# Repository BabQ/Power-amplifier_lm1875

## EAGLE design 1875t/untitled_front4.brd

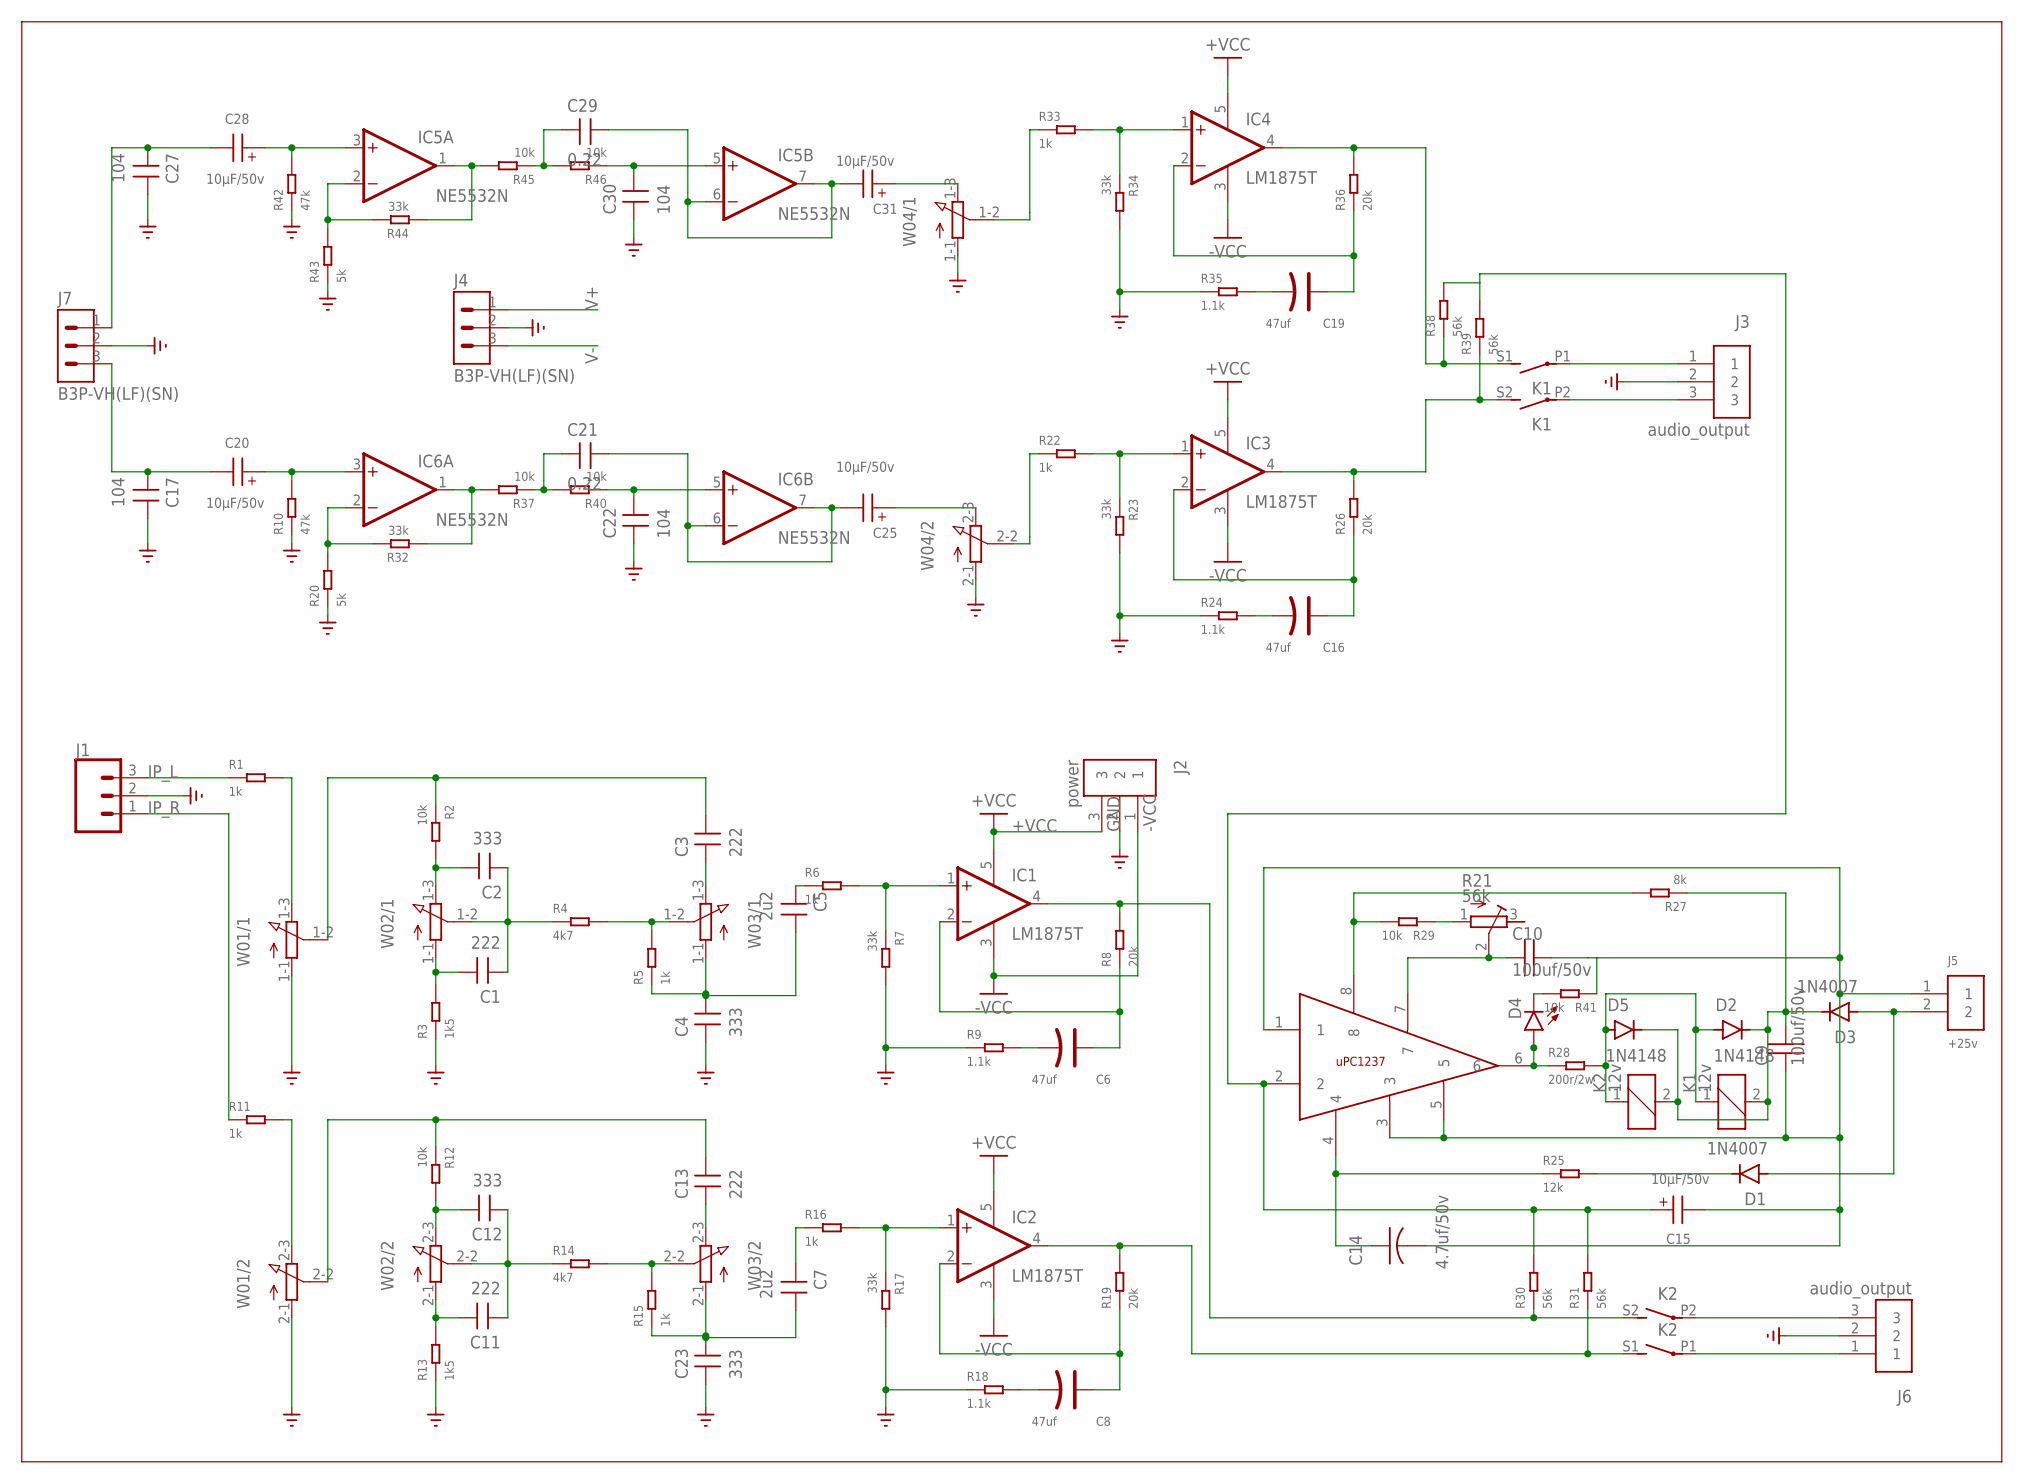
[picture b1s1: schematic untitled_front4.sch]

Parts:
C1, C3, C11, C13: 222; 5.08MM-独石电容
C2, C4, C12, C23: 333; 5.08MM-独石电容
C5, C7: 2u2; 5.08MM-独石电容
C6, C8, C16, C19: 47uf; PC-D5.3MM
C9, C10: 100uf/50v; 8X12
C14: 4.7uf/50v; CAP_RADIAL_2MM
C15, C20, C25, C28, C31: 10µF/50v; WCAP-AT1H_5X11(DXL)
C17, C22, C27, C30: 104; 5.08MM-独石电容
C21, C29: 0.22; 5.08MM-独石电容
D1, D3: 1N4007; DO-41
D2, D5: 1N4148; DO-41
D4: BEAGLEBONE_BLUE_LED-3MM-NO_SILK; BEAGLEBONE_BLUE_BEAGLEBONE_BLUE_LED3MM-NS
IC1, IC2, IC3, IC4: LM1875T; CB367
IC5, IC6: NE5532N; DIL08
J1: CONN_03POLAR; MOLEX-1X3
J2: power; TERMINALBLOCK_PLUGGABLE-3-7.62MM
J3, J6: audio_output; TERMINALBLOCK_PLUGGABLE-3-7.62MM
J4, J7: B3P-VH(LF)(SN); HDR-03
J5: +25v; S2B-PH-K-S(LF)(SN)
K1, K2: 12v; G2R2A
R1, R5, R6, R11, R15, R16, R22, R33: 1k; PR-D2.3XL6.5MM
R2, R12, R29, R37, R40, R41, R45, R46: 10k; PR-D2.3XL6.5MM
R3, R13: 1k5; PR-D2.3XL6.5MM
R4, R14: 4k7; PR-D2.3XL6.5MM
R7, R17, R23, R32, R34, R44: 33k; PR-D2.3XL6.5MM
R8, R19, R26, R36: 20k; PR-D2.3XL6.5MM
R9, R18, R24, R35: 1.1k; PR-D2.3XL6.5MM
R10, R42: 47k; PR-D2.3XL6.5MM
R20, R43: 5k; PR-D2.3XL6.5MM
R21: 56k; RTRIM3296W
R25: 12k; PR-D2.3XL6.5MM
R27: 8k; PR-D2.3XL6.5MM
R28: 200r/2w; PR-D2.3XL6.5MM
R30, R31, R38, R39: 56k; PR-D2.3XL6.5MM
U2: UPC1237HA; SIP8
W01, W02, W03, W04: 3RP/1610G

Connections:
+VCC: IC1.5 (V+), IC2.5 (V+), IC3.5 (V+), IC4.5 (V+), J2.3
-VCC: IC1.3 (V-), IC2.3 (V-), IC3.3 (V-), IC4.3 (V-), J2.1
GND: C4.P$2 (1), C17.P$1 (2), C22.P$2 (1), C23.P$2 (1), C27.P$1 (2), C30.P$2 (1), J1.2, J2.2, J3.2, J4.2, J6.2, J7.2, R3.1, R7.2, R9.1, R10.1, R13.1, R17.2, R18.1, R20.1, R23.2, R24.1, R34.2, R35.1, R42.1, R43.1, W01.1-1 (A), W01.2-1 (A), W04.1-1 (A), W04.2-1 (A)
IP_L: J1.3, R1.1
IP_R: J1.1, R11.1
unnamed: R1.2, W01.1-3 (E)
unnamed: D4.K (C), R41.2
unnamed: C2.P$1 (2), R2.2, W02.1-3 (E)
unnamed: C1.P$1 (2), R3.2, W02.1-1 (A)
unnamed: R4.2, R5.2, W03.1-2 (S)
unnamed: C1.P$2 (1), C2.P$2 (1), R4.1, W02.1-2 (S)
unnamed: IC1.1 (+IN), R6.2, R7.1
unnamed: C4.P$1 (2), C5.P$1 (2), R5.1, W03.1-1 (A)
unnamed: IC1.4 (OUT), K2.S2 (S), R8.2, R30.1
unnamed: C6.+, IC1.2 (-IN), R8.1
unnamed: C5.P$2 (1), R6.1
unnamed: C6.-, R9.2
unnamed: C17.P$2 (1), C20.2 (-), J7.3
unnamed: C3.P$2 (1), W03.1-3 (E)
unnamed: R11.2, W01.2-3 (E)
unnamed: C27.P$2 (1), C28.2 (-), J7.1
unnamed: C12.P$1 (2), R12.2, W02.2-3 (E)
unnamed: C11.P$1 (2), R13.2, W02.2-1 (A)
unnamed: R14.2, R15.2, W03.2-2 (S)
unnamed: C11.P$2 (1), C12.P$2 (1), R14.1, W02.2-2 (S)
unnamed: C7.P$1 (2), C23.P$1 (2), R15.1, W03.2-1 (A)
unnamed: IC2.1 (+IN), R16.2, R17.1
unnamed: IC2.4 (OUT), K2.S1 (S), R19.2, R31.1
unnamed: C8.+, IC2.2 (-IN), R19.1
unnamed: C7.P$2 (1), R16.1
unnamed: C8.-, R18.2
unnamed: C20.1 (+), IC6.3 (+IN), R10.2
unnamed: C13.P$2 (1), W03.2-3 (E)
unnamed: J6.1, K2.P1
unnamed: J6.3, K2.P2
unnamed: D1.C, R25.2
unnamed: C10.1, R21.2 (S), U2.7
unnamed: R33.1, W04.1-2 (S)
unnamed: IC3.1 (+IN), R22.2, R23.1
unnamed: IC3.4 (OUT), K1.S2 (S), R26.2, R39.1
unnamed: C16.+, IC3.2 (-IN), R26.1
unnamed: R22.1, W04.2-2 (S)
unnamed: C16.-, R24.2
unnamed: IC6.2 (-IN), R20.2, R32.2
unnamed: D1.A, D3.A, J5.2
unnamed: D4.A, R28.1, U2.6
unnamed: D2.A, D5.A, K1.1, K2.1, R28.2
unnamed: C9.2, D2.C, D3.C, D5.C, K1.2, K2.2, R27.1
unnamed: R27.2, R29.2, U2.8
unnamed: R21.1 (A), R29.1
unnamed: J3.3, K1.P2
unnamed: C14.1, R25.1, U2.4
unnamed: C15.1 (+), R30.2, R31.2, R38.2, R39.2, U2.2
unnamed: C28.1 (+), IC5.3 (+IN), R42.2
unnamed: IC4.1 (+IN), R33.2, R34.1
unnamed: IC4.4 (OUT), K1.S1 (S), R36.2, R38.1
unnamed: C19.+, IC4.2 (-IN), R36.1
unnamed: C3.P$1 (2), R2.1, W01.1-2 (S)
unnamed: C19.-, R35.2
unnamed: IC6.1 (OUT), R32.1, R37.2
unnamed: C9.1, C10.2, C14.2, C15.2 (-), J5.1, R41.1, U2.1, U2.3, U2.5
unnamed: J3.1, K1.P1
unnamed: C13.P$1 (2), R12.1, W01.2-2 (S)
unnamed: C21.P$2 (1), R37.1, R40.2
unnamed: C22.P$1 (2), IC6.5 (+IN), R40.1
unnamed: C21.P$1 (2), C25.2 (-), IC6.6 (-IN), IC6.7 (OUT)
unnamed: C29.P$1 (2), C31.2 (-), IC5.6 (-IN), IC5.7 (OUT)
unnamed: IC5.2 (-IN), R43.2, R44.2
unnamed: IC5.1 (OUT), R44.1, R45.2
unnamed: C29.P$2 (1), R45.1, R46.2
unnamed: C30.P$1 (2), IC5.5 (+IN), R46.1
unnamed: C31.1 (+), W04.1-3 (E)
unnamed: C25.1 (+), W04.2-3 (E)
V+: IC5.8 (V+), IC6.8 (V+), J4.1
V-: IC5.4 (V-), IC6.4 (V-), J4.3

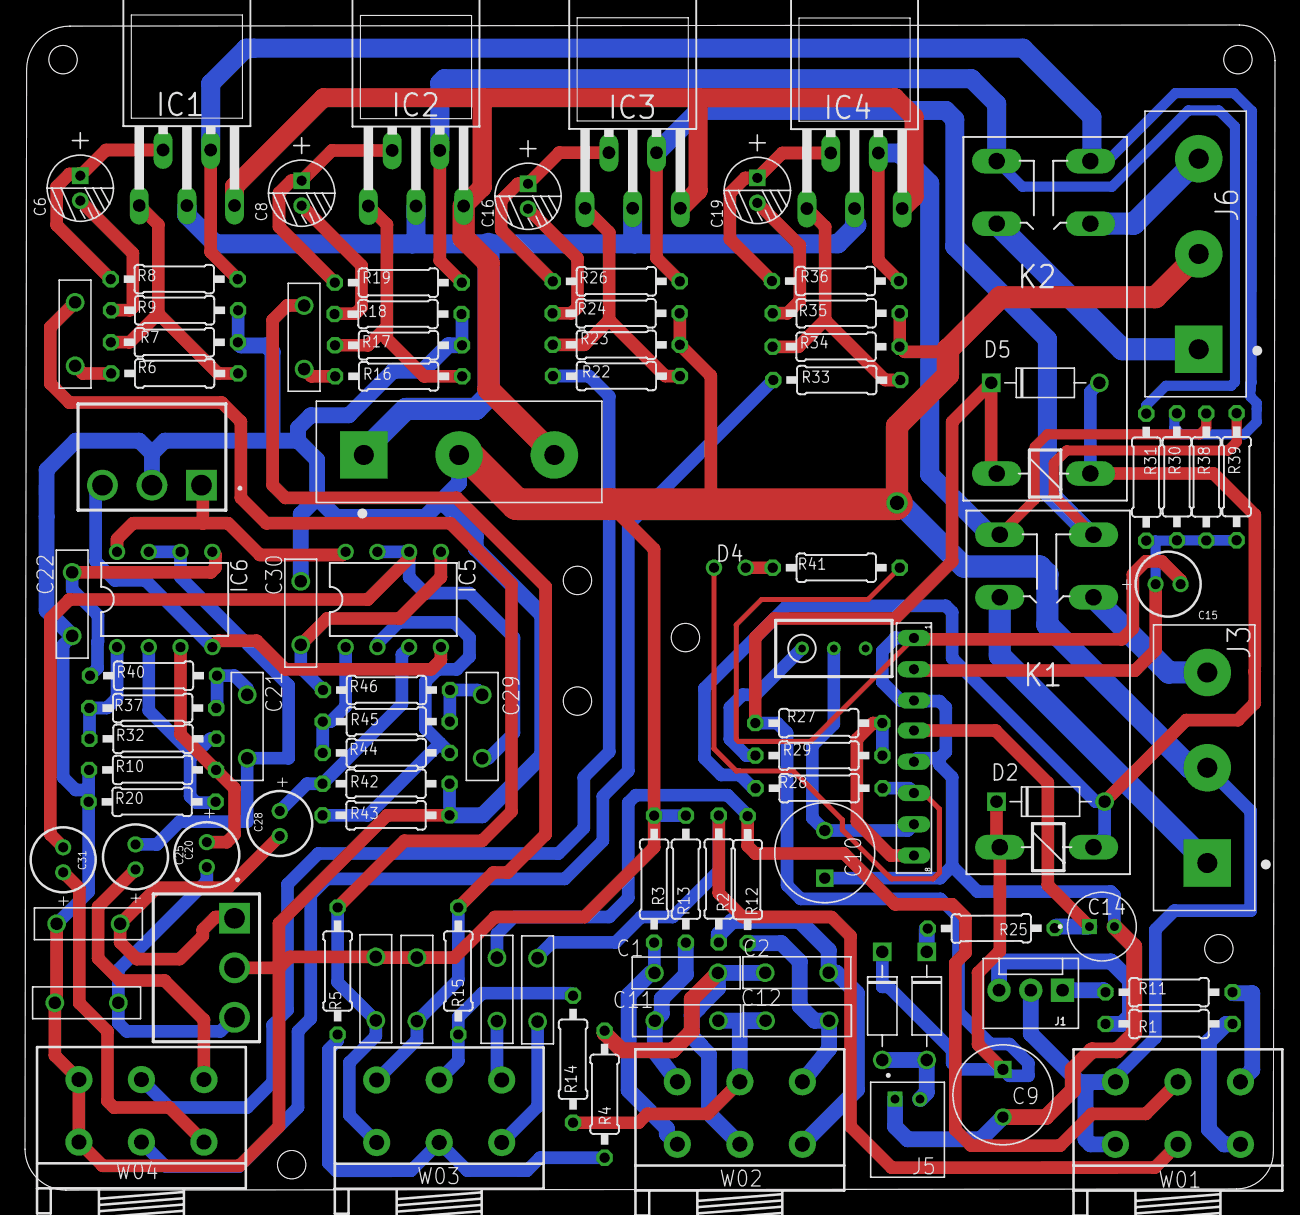
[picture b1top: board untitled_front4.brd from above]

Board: 2 copper layers, 100.0 x 93.2 mm, 99 parts (0 on the bottom side), 75 nets.

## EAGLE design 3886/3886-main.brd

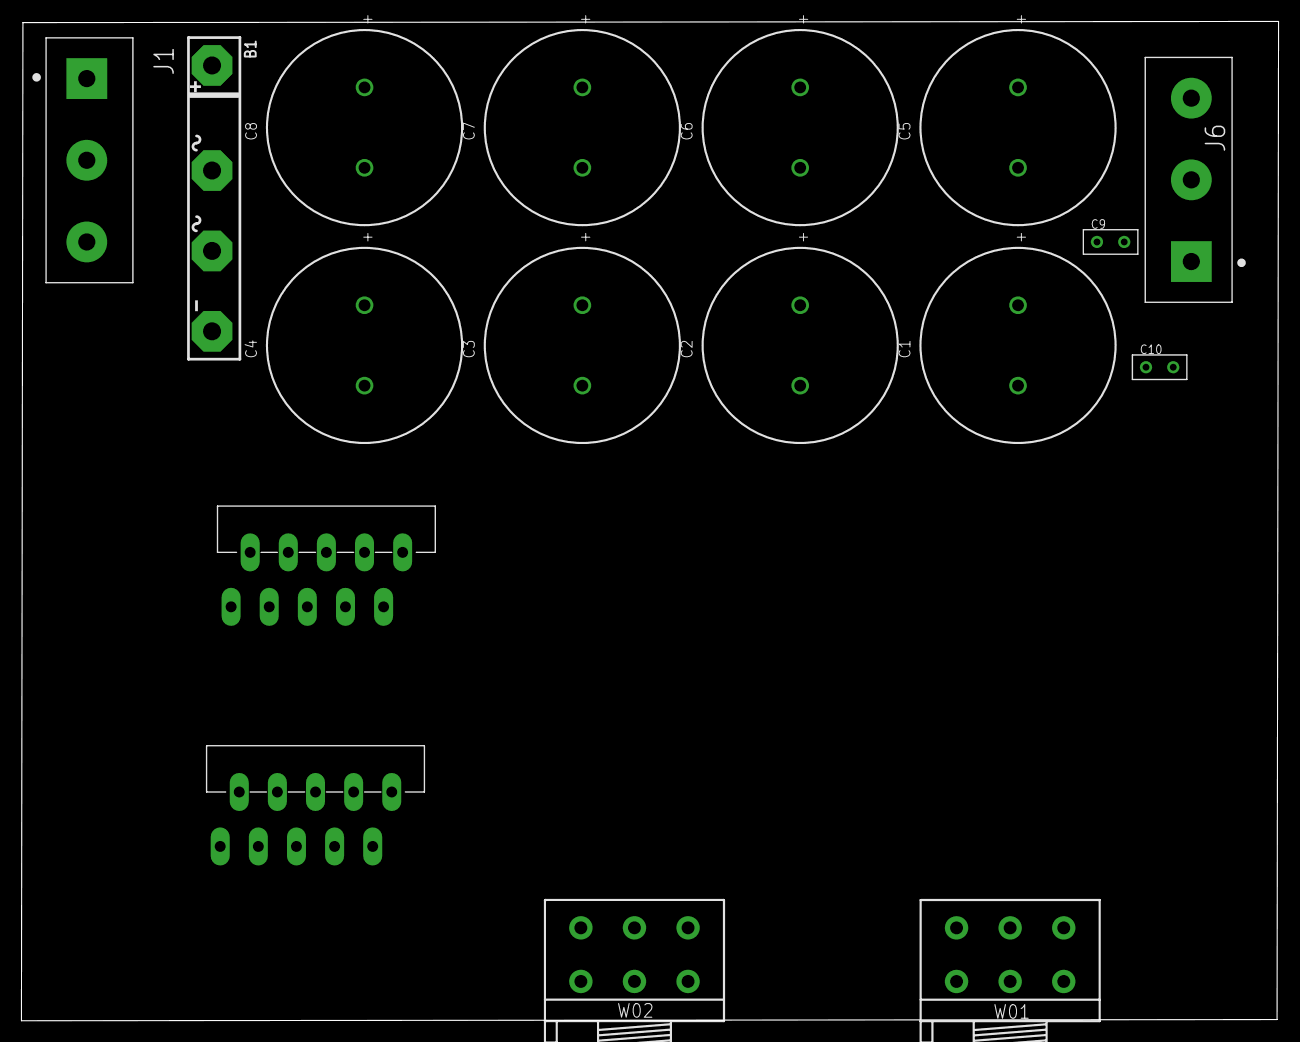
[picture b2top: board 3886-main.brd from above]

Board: 2 copper layers, 117.3 x 93.2 mm, 18 parts (0 on the bottom side), 9 nets, no tracks yet.

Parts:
B1: GBJ25; GBJ
C1, C2, C3, C4, C5, C6, C7, C8: 3300 µF; WCAP-ATG5_18X35.5(DXL)
C9, C10: 100nf; CERAMIC-2.54
FRAME1: FRAME-LEDGER; CREATIVE_COMMONS
J1, J6: audio_output; TERMINALBLOCK_PLUGGABLE-3-7.62MM
U$1, U$2: TO220-11
W01, W02: 3RP/1610G

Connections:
1: U$1.1, U$2.1
4: U$1.4, U$2.4
5: U$1.5, U$2.5
7: U$1.7, U$2.7
unnamed: B1.AC2, J1.3
unnamed: B1.AC1, J1.1
unnamed: C1.2, C2.2, C3.2, C4.2, C5.1, C6.1, C7.1, C8.1, C9.1, C10.2, J1.2
unnamed: B1.+, C1.1, C2.1, C3.1, C4.1, C9.2
unnamed: B1.-, C5.2, C6.2, C7.2, C8.2, C10.1

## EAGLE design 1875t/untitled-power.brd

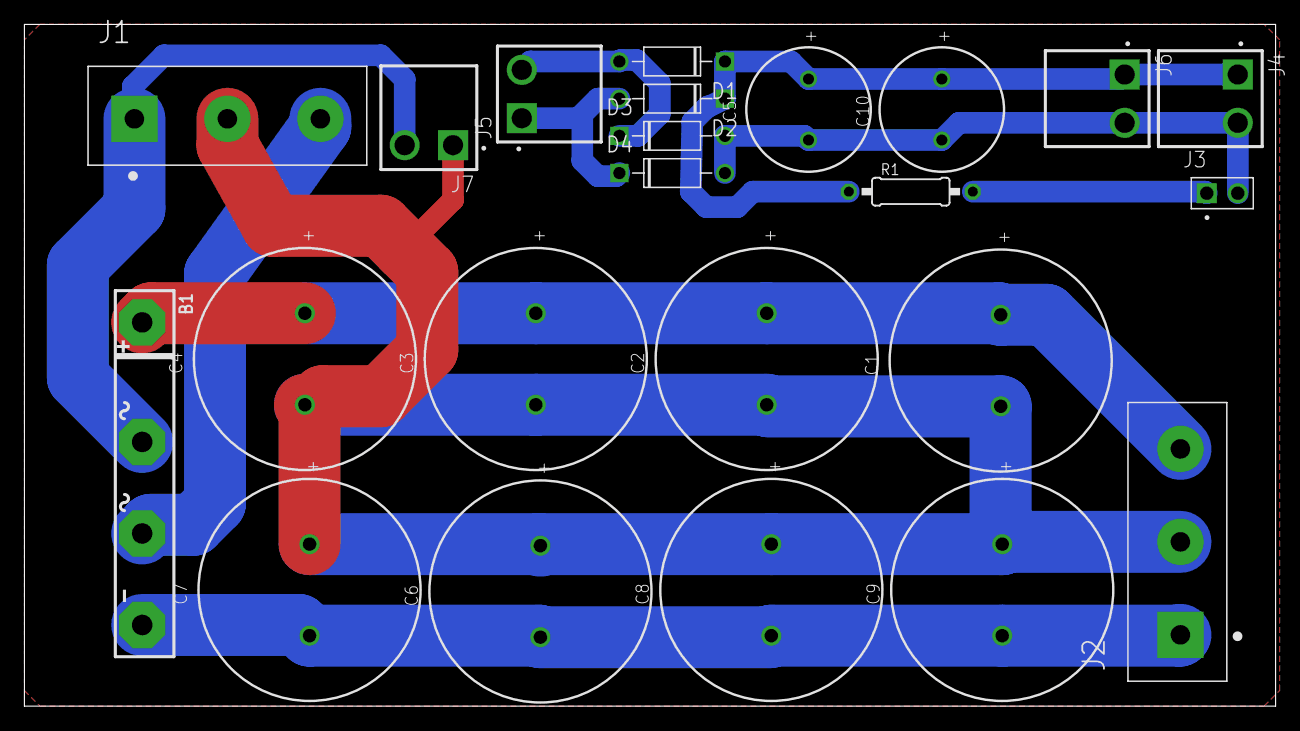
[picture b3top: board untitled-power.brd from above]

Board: 2 copper layers, 102.5 x 55.9 mm, 23 parts (0 on the bottom side), 10 nets.

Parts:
B1: GBJ25; GBJ
C1, C2, C3, C4, C6, C7, C8, C9: 330 µF; WCAP-AT1H_18X35.5(DXL)
C5, C10: 1000 µF; WCAP-ATET_10X25(DXL)
D1, D2, D3, D4: 1N4007; DO-41
J1: in_+-25v; TERMINALBLOCK_PLUGGABLE-3-7.62MM
J2: out_+-25v; TERMINALBLOCK_PLUGGABLE-3-7.62MM
J3: LED; 61300211121
J4, J6, J7: out_12v; HDR-02
J5: in_12v; HDR-02
R1: 5k; PR-D2.3XL6.5MM

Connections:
GND: C1.2, C2.2, C3.2, C4.2, C6.1, C7.1, C8.1, C9.1, J1.2, J2.2, J7.1
unnamed: D2.A, D4.C, J5.1
unnamed: J3.1, R1.2
unnamed: B1.AC1, J1.1, J7.2
unnamed: B1.AC2, J1.3
unnamed: B1.+, C1.1, C2.1, C3.1, C4.1, J2.3
unnamed: B1.-, C6.2, C7.2, C8.2, C9.2, J2.1
unnamed: D1.A, D3.C, J5.2
unnamed: C5.1, C10.1, D1.C, D2.C, J4.1, J6.1, R1.1
unnamed: C5.2, C10.2, D3.A, D4.A, J3.2, J4.2, J6.2

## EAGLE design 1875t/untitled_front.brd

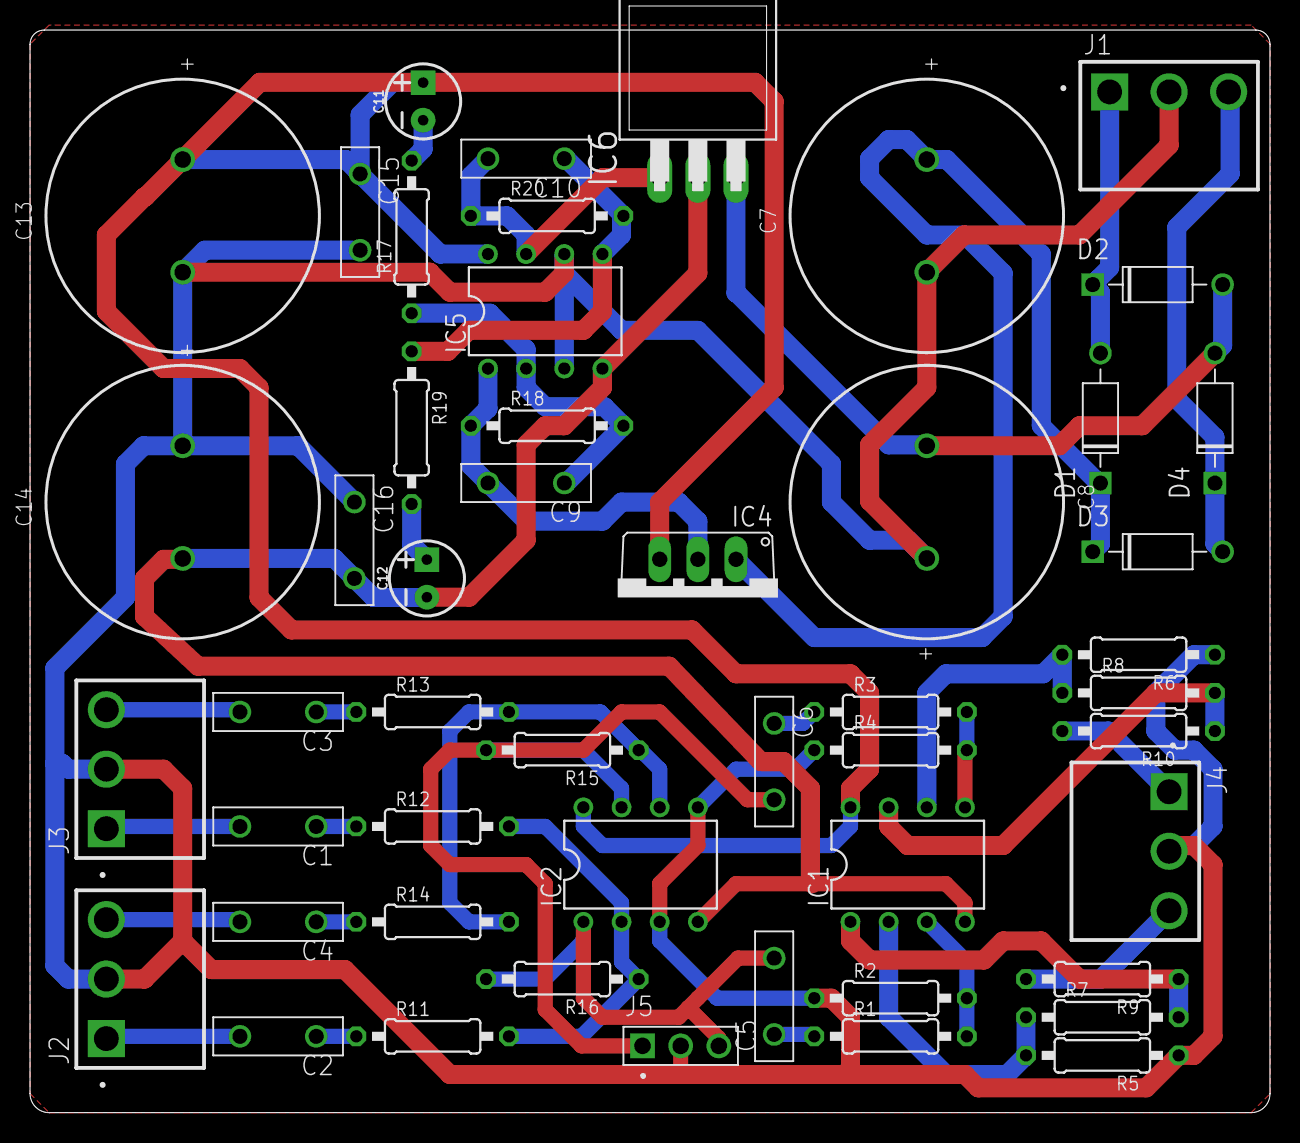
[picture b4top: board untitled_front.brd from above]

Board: 2 copper layers, 82.5 x 72.1 mm, 50 parts (0 on the bottom side), 35 nets.

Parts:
C1, C2, C3, C4: 1u; 5.08MM-独石电容
C5, C6: 10u; 5.08MM-独石电容
C7, C8, C13, C14: 330 µF; WCAP-AT1H_18X35.5(DXL)
C9, C10: 33p; 5.08MM-独石电容
C11, C12: 10uF; CPOL-RADIAL-2.5MM-5MM
C15, C16: 0.1; 5.08MM-独石电容
D1, D2, D3, D4: 1N4007; DO-41
IC1, IC2, IC5: NE5532N; DIL08
IC4: 7812TV; TO220V
IC6: 7912; TO220H
J1: power_source; HDR-03
J2: input1; HDR-03
J3: input2; HDR-03
J4: output; HDR-03
J5: 61300311121
R1, R3, R9, R10, R17, R19: 1k; PR-D2.3XL6.5MM
R2, R4: 47k; PR-D2.3XL6.5MM
R5, R6: 10k; PR-D2.3XL6.5MM
R7, R8, R11, R12, R13, R14, R15, R16: 100k; PR-D2.3XL6.5MM
R18, R20: 33k; PR-D2.3XL6.5MM

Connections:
GND: C7.2, C8.1, C13.2, C14.1, C15.P$2, C16.P$1, IC2.3, IC2.5, IC5.3, IC5.6, J1.2, J2.2, J3.2, J4.2, J5.2, R2.1, R4.1, R5.1, R6.1
I1_L: C2.P$2, J2.1
I1_R: C4.P$2, J2.3
I2_L: C1.P$2, J3.1
I2_R: C3.P$2, J3.3
L_OUT: C5.P$1, R1.1
unnamed: IC1.6, R6.2, R8.1
unnamed: IC1.2, R5.2, R7.1
unnamed: IC1.3, R1.2, R2.2
unnamed: IC1.5, R3.2, R4.2
unnamed: IC1.7, R8.2, R10.1
unnamed: IC1.1, R7.2, R9.1
unnamed: J4.1, R10.2
unnamed: J4.3, R9.2
unnamed: D1.A, D2.C, J1.1
unnamed: C3.P$1, R13.1
unnamed: C1.P$1, R12.1
unnamed: C2.P$1, R11.1
unnamed: C4.P$1, R14.1
unnamed: IC2.6, R13.2, R14.2, R15.1
unnamed: IC2.2, R11.2, R12.2, R16.1
unnamed: C6.P$2, IC2.7, J5.1, R15.2
unnamed: C5.P$2, IC2.1, J5.3, R16.2
unnamed: D3.A, D4.C, J1.3
unnamed: C8.2, D2.A, D4.A, IC6.3
unnamed: C7.1, D1.C, D3.C, IC4.1
unnamed: C9.P$2, IC4.2, IC5.1, R18.1
unnamed: C10.P$1, IC5.5, R19.1, R20.2
unnamed: C9.P$1, IC5.2, R17.1, R18.2
unnamed: C10.P$2, IC5.7, IC6.1, R20.1
unnamed: C12.1, R19.2
unnamed: C11.2, R17.2
R_OUT: C6.P$1, R3.1
V+: C11.1, C13.1, C15.P$1, IC1.8, IC2.8, IC4.3, IC5.8
V-: C12.2, C14.2, C16.P$2, IC1.4, IC2.4, IC5.4, IC6.2

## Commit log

2020-08-09 后级放大:再加一对重低音用
2020-08-09 后级放大:更新
2020-08-09 clean
2020-08-13 后级：更新upc1237保护电路
2020-08-30 add readme.md
2020-08-30 cleaning
2020-10-01 add:a new pcb project for 3886

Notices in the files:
parts and their libraries:
Wurth_Capacitors_WCAP-AT1H: Copyright: Würth Elektronik
SparkFun-Capacitors: Licensing: Creative Commons ShareAlike 4.0 International - https://creativecommons.org/licenses/by-sa/4.0
SparkFun-Aesthetics: Released under the Creative Commons Attribution Share-Alike 4.0 License
